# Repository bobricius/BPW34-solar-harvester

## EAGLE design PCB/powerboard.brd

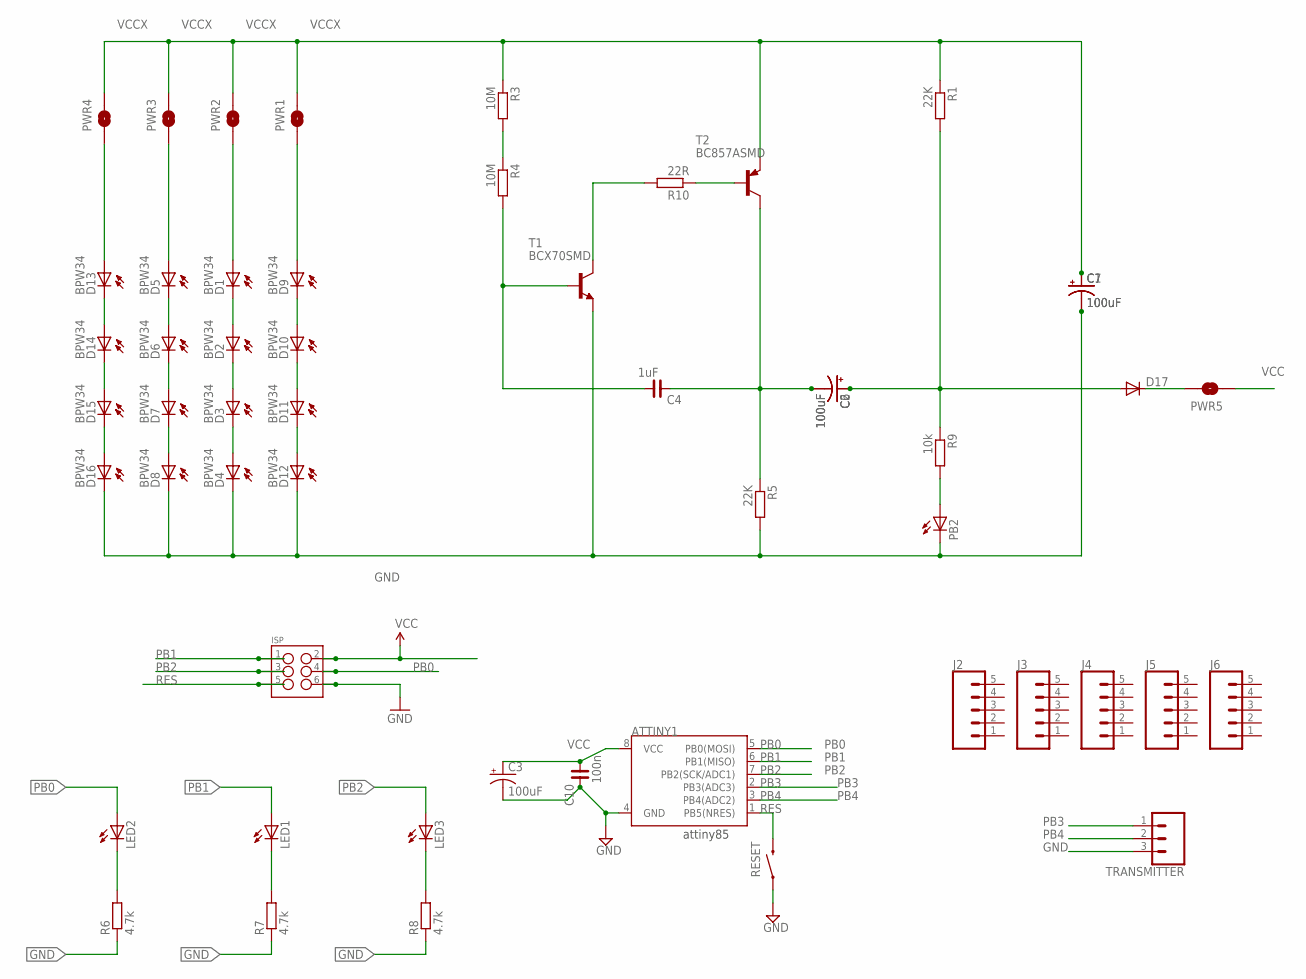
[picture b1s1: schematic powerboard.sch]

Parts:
ATTINY1: ATTINY45DIP8; DIP08
C1, C2, C3: 100uF; CPOL-RADIAL-10UF-25V
C4: 1uF; C0805
C6, C7: 100uF; EIA3216
C10: 100n; C1206
D1, D2, D3, D4, D5, D6, D7, D8, D9, D10, D11, D12, D13, D14, D15, D16: BPW34; BP104
D17: DIODE-DO214AA; DO214AA
ISP: M03X2NO_SILK; 2X3-NS@1
J2, J3, J4, J5, J6: CONN_05NO_SILK; 1X05_NO_SILK
LED1, LED2, LED3: LEDCHIPLED_1206; CHIPLED_1206
PB2: LEDKA-3528ASYC; KA-3528ASYC
PWR1, PWR2, PWR3, PWR4, PWR5: SOLDERJUMPERNO; SJ_2S-NO
R1, R5: 22K; R0805W
R3, R4: 10M; R0805W
R6, R7, R8: 4.7k; R1206W
R9: 10k; R0805W
R10: 22R; R0805
RESET: SWITCH-MOMENTARY-2PTH; TACTILE-PTH
T1: BCX70SMD; SOT23
T2: BC857ASMD; SOT23-BEC
TRANSMITTER: CONN_03LONGPADS; 1X03_LONGPADS

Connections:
GND: ATTINY1.4 (GND), C1.2 (-), C3.2 (-), C7.C (-), C10.2, D4.K (C), D8.K (C), D12.K (C), D16.K (C), ISP.6, PB2.C, R5.2, R6.1, R7.1, R8.1, RESET.1, T1.2 (E), TRANSMITTER.3
unnamed: R10.1, T2.B
unnamed: R10.2, T1.3 (C)
unnamed: D9.A, PWR1.1
unnamed: C2.1 (+), C6.A (+), D17.A, R1.2, R9.1
unnamed: R3.2, R4.1
unnamed: LED2.C, R6.2
unnamed: D9.K (C), D10.A
unnamed: D10.K (C), D11.A
unnamed: C2.2 (-), C4.2, C6.C (-), R5.1, T2.C
unnamed: D11.K (C), D12.A
unnamed: D1.A, PWR2.1
unnamed: D1.K (C), D2.A
unnamed: D2.K (C), D3.A
unnamed: D3.K (C), D4.A
unnamed: D5.A, PWR3.1
unnamed: D5.K (C), D6.A
unnamed: D6.K (C), D7.A
unnamed: D7.K (C), D8.A
unnamed: D13.A, PWR4.1
unnamed: D13.K (C), D14.A
unnamed: D14.K (C), D15.A
unnamed: D15.K (C), D16.A
unnamed: LED1.C, R7.2
unnamed: LED3.C, R8.2
unnamed: PB2.A, R9.2
unnamed: D17.C, PWR5.2
PB0: ATTINY1.5 (PB0(MOSI)), ISP.4, LED2.A
PB1: ATTINY1.6 (PB1(MISO)), ISP.1, LED1.A
PB2: ATTINY1.7 (PB2(SCK/ADC1)), ISP.3, LED3.A
PB3: ATTINY1.2 (PB3(ADC3)), TRANSMITTER.1
PB4: ATTINY1.3 (PB4(ADC2)), TRANSMITTER.2
RES: ATTINY1.1 (PB5(NRES)), ISP.5, RESET.3 (2)
VCC: ATTINY1.8 (VCC), C3.1 (+), C10.1, ISP.2, PWR5.1
VCCX: C1.1 (+), C7.A (+), PWR1.2, PWR2.2, PWR3.2, PWR4.2, R1.1, R3.1, T2.E
XX: C4.1, R4.2, T1.1 (B)

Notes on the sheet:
attiny85

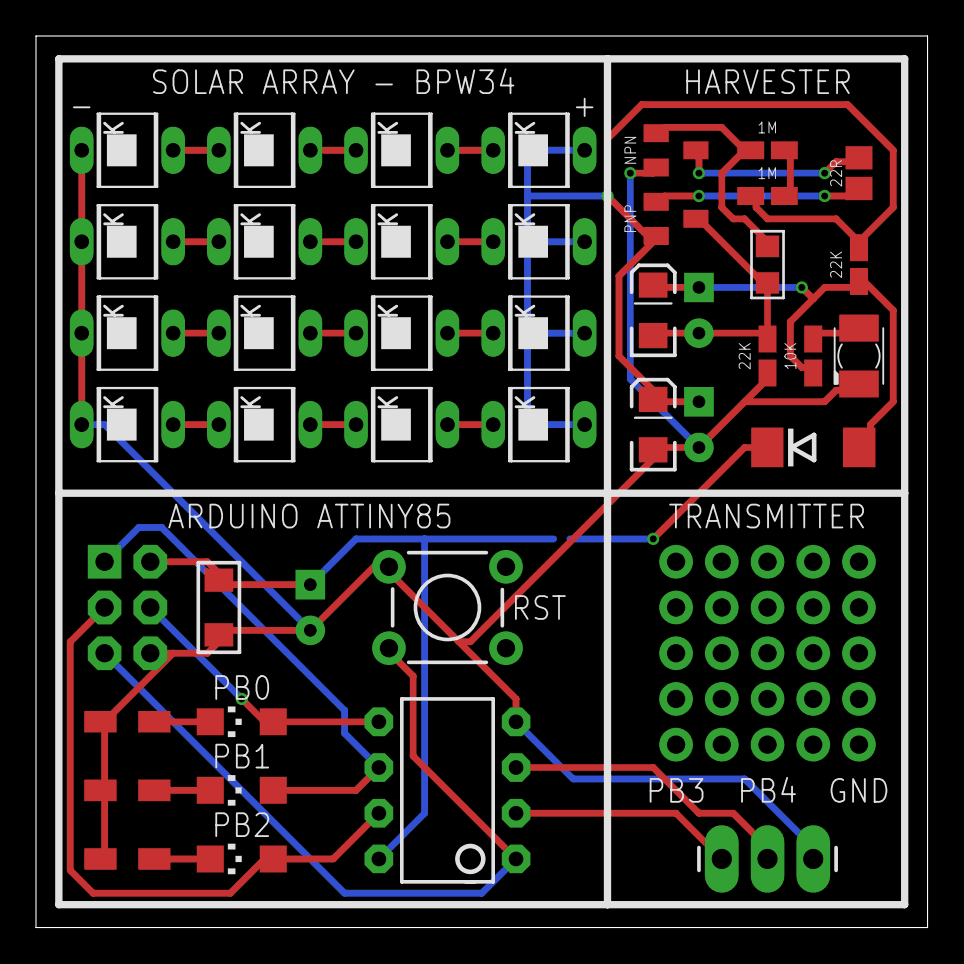
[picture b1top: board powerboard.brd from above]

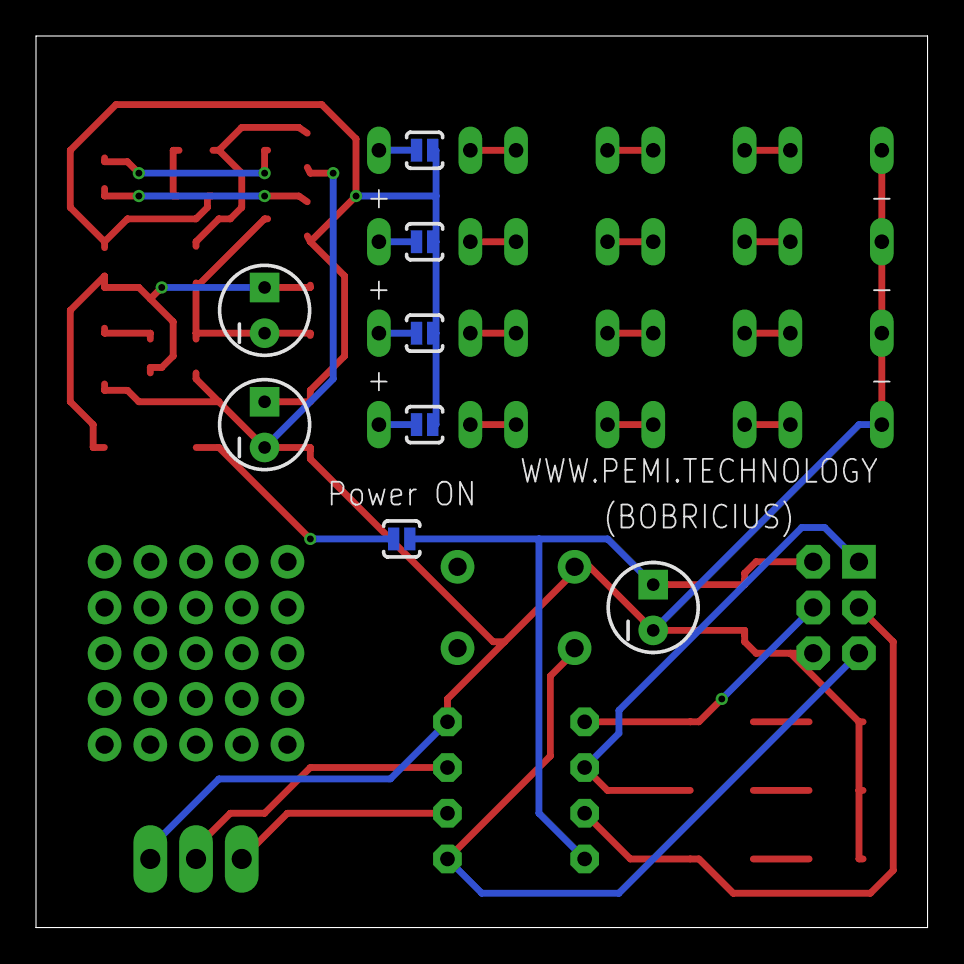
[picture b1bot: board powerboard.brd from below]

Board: 2 copper layers, 49.5 x 49.5 mm, 53 parts (8 on the bottom side), 36 nets.

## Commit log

2018-07-15 First upload
    Ultra low power energy harvester from BPW34

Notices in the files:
parts and their libraries:
SparkFun: Licensing: CC v3.0 Share-Alike You are welcome to use this library for commercial purposes.
SparkFun-Connectors: Licensing: Creative Commons ShareAlike 4.0 International - https://creativecommons.org/licenses/by-sa/4.0
